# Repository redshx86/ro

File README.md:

The control box i made for my reverse osmosis filter. I doubt anyone needs this.

## Main display
Off -> Blank\
Idle -> filter total time, days\
Work -> filtering time, minutes\
Flush -> Spin\
No water -> "drY"\
Timeout -> "Err"\
Short press: Off->on, Flush/Nowater/Timeout->idle, Other->lamp on/off\
Long press: menu\

### Menu
OFF -> Turn off\
FLU -> Start manual flush\
C00 -> Filter total time, hrs/thousands\
C01 -> Filter work time, hrs/thousands\
C02 -> Total on time, hrs/thousands\
C03 -> Total run time, hrs/thousands\
C04 -> Total start count, pcs/thousands\
C05 -> Total flush count, pcs/thousands\
P00 -> Manual flushing time 0..60/1 min\
P01 -> Auto flushing time 0..900/10 sec\
P02 -> Work time flush threshold 0..990/10 min\
P03 -> Total time flush threshold 0..240/5 hr\
P04 -> Timeout 0..360/5 min\
P05 -> Nowater delay 0..60/1 sec\
P06 -> Extra work time after HP switch off 0..360/5 sec\
CLr -> Reset filter on time/work time (confirm yes/no)\
X.XX -> AIN_C voltage (ok=back)\
XX.X -> Input voltage (ok=back)\
Long press: edit parameter/ok\
Short press: next parameter\

### Parameter edit / confirm menu\
short press: increase value / toggle confirm\
long press: save\

### Parameter display\
short press: back to menu\
long press: back to main display\

## Board pinout
DIA -> low pressure switch\
DIB -> high pressure switch\
DQA -> pump + inlet valve\
DQB -> flush valve\
DQC -> lamp\

## ATmega328 fuses
int.RC 8MHz 0ms+6CK DIV8\
BOR@1.8V

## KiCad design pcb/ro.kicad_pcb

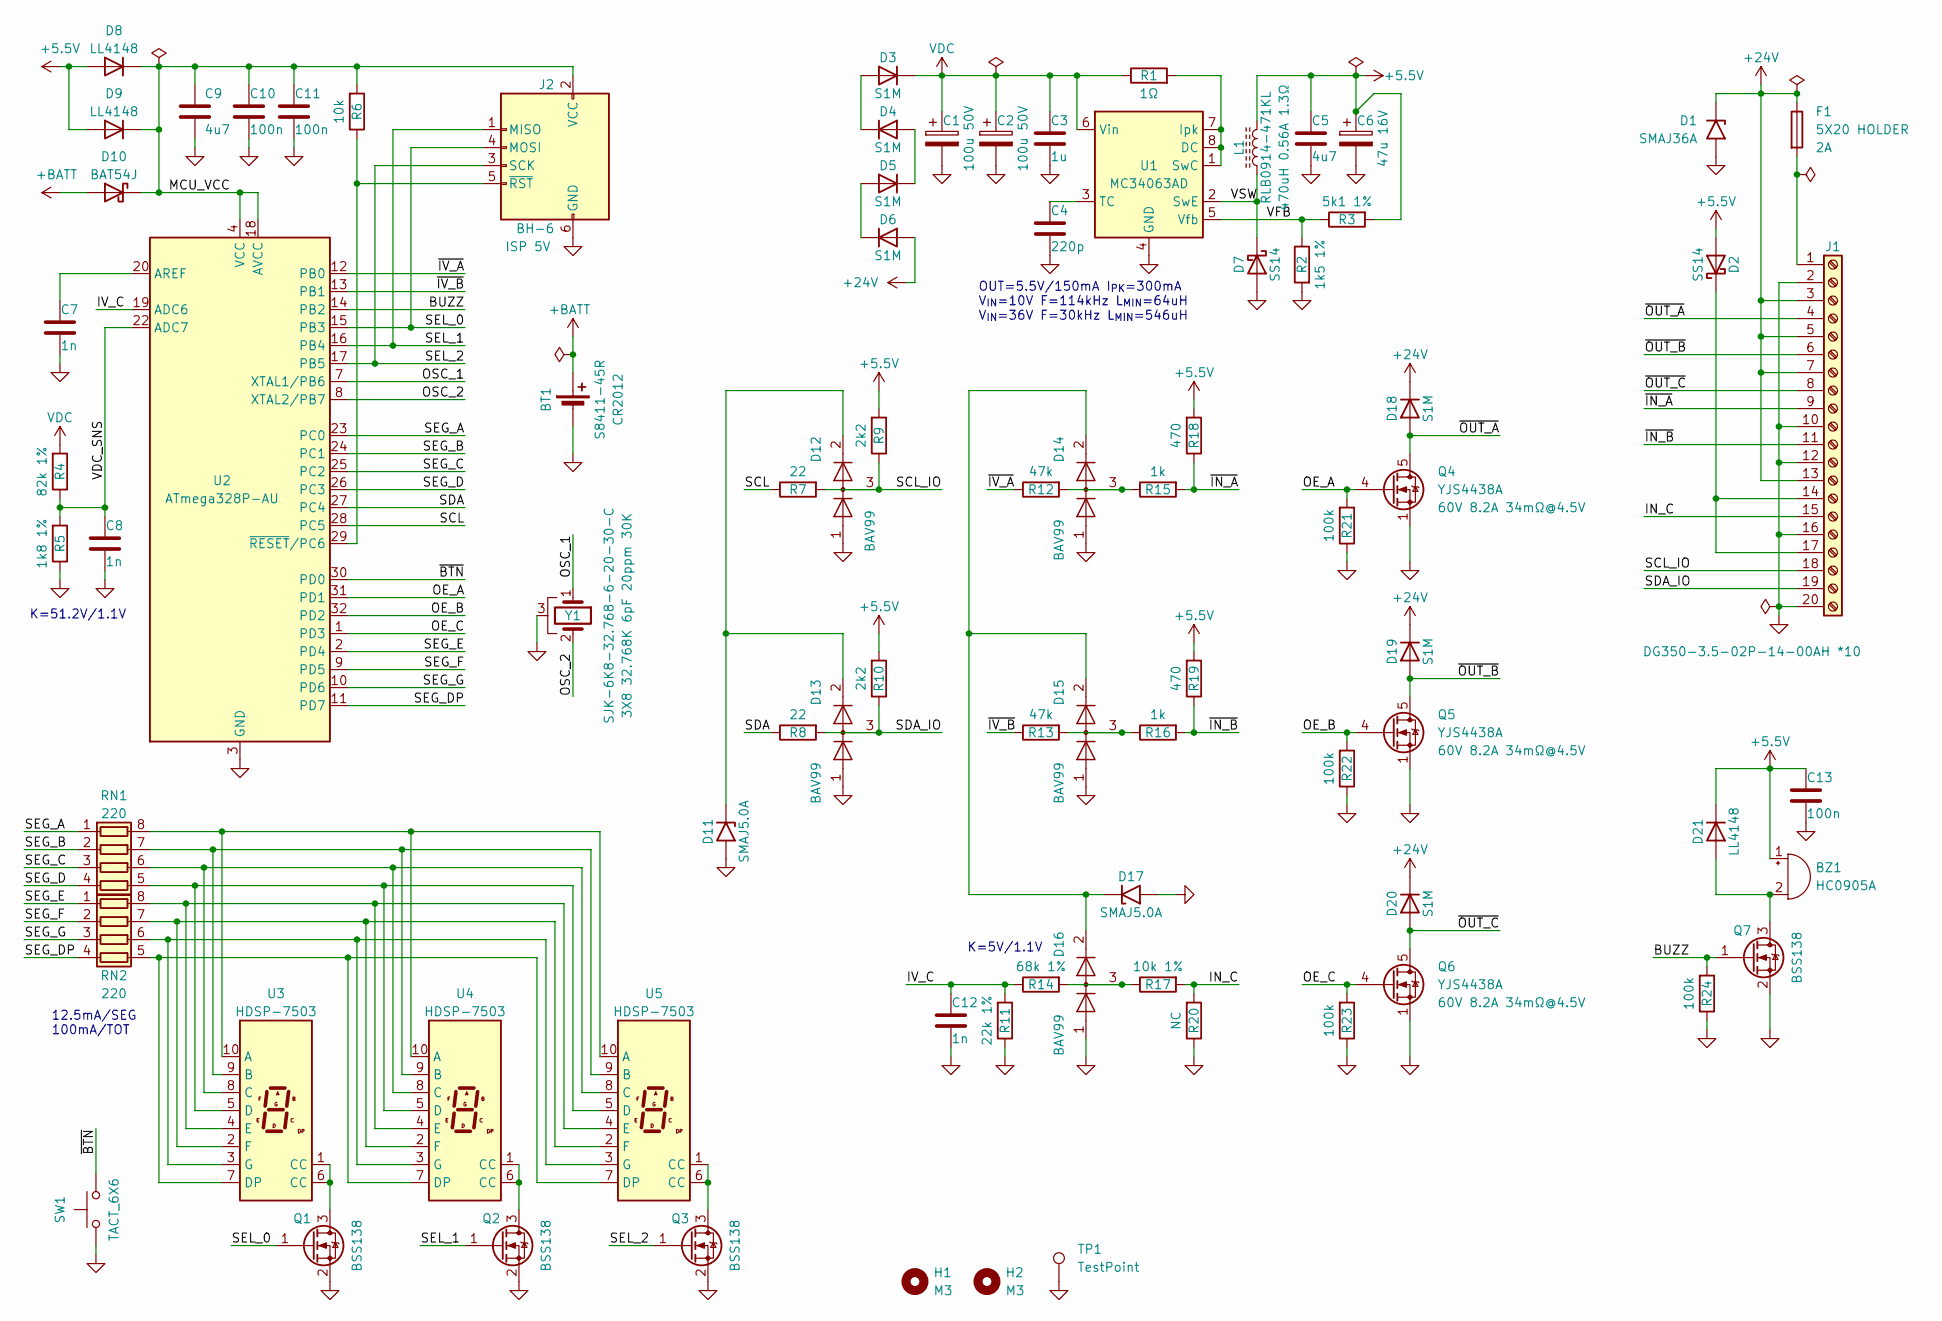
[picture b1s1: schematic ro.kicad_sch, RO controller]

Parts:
BT1: S8411-45R
BZ1: HC0905A; MagneticBuzzer_CUI_CST-931RP-A
C1, C2: 100u 50V; CP_Elec_8x10.5
C3: 1u; C_1206_3216Metric_Pad1.33x1.80mm_HandSolder
C4: 220p; C_0603_1608Metric_Pad1.08x0.95mm_HandSolder
C5, C9: 4u7; C_1206_3216Metric_Pad1.33x1.80mm_HandSolder
C6: 47u 16V; CP_EIA-7343-31_Kemet-D_Pad2.25x2.55mm_HandSolder
C7, C8, C12: 1n; C_0603_1608Metric_Pad1.08x0.95mm_HandSolder
C10, C11, C13: 100n; C_0603_1608Metric_Pad1.08x0.95mm_HandSolder
D1: SMAJ36A; D_SMA
D2, D7: SS14; D_SMA
D3, D4, D5, D6, D18, D19, D20: S1M; D_SMA
D8, D9, D21: LL4148; D_MiniMELF
D10: BAT54J; D_SOD-323_HandSoldering
D11, D17: SMAJ5.0A; D_SMA
D12, D13, D14, D15, D16: BAV99; SOT-23
F1: 5X20 HOLDER; Fuse_Clip_TE_520
H1, H2: M3; MountingHole_3.2mm_M3
J1: DG350-3.5-02P-14-00AH *10; TerminalBlock_4Ucon_1x20_P3.50mm_Horizontal
J2: BH-6; IDC-Header_2x03_P2.54mm_Vertical
L1: RLB0914-471KL; L_Radial_D8.7mm_P5.00mm_Fastron_07HCP
Q1, Q2, Q3, Q7: BSS138; SOT-23
Q4, Q5, Q6: YJS4438A; SOIC-8_3.9x4.9mm_P1.27mm
R1: 1Ω; R_1206_3216Metric_Pad1.30x1.75mm_HandSolder
R2: 1k5 1%; R_0603_1608Metric_Pad0.98x0.95mm_HandSolder
R3: 5k1 1%; R_0603_1608Metric_Pad0.98x0.95mm_HandSolder
R4: 82k 1%; R_0603_1608Metric_Pad0.98x0.95mm_HandSolder
R5: 1k8 1%; R_0603_1608Metric_Pad0.98x0.95mm_HandSolder
R6: 10k; R_0603_1608Metric_Pad0.98x0.95mm_HandSolder
R7, R8: 22; R_0603_1608Metric_Pad0.98x0.95mm_HandSolder
R9, R10: 2k2; R_0603_1608Metric_Pad0.98x0.95mm_HandSolder
R11: 22k 1%; R_0603_1608Metric_Pad0.98x0.95mm_HandSolder
R12, R13: 47k; R_0603_1608Metric_Pad0.98x0.95mm_HandSolder
R14: 68k 1%; R_0603_1608Metric_Pad0.98x0.95mm_HandSolder
R15, R16: 1k; R_0603_1608Metric_Pad0.98x0.95mm_HandSolder
R17: 10k 1%; R_0603_1608Metric_Pad0.98x0.95mm_HandSolder
R18, R19: 470; R_0603_1608Metric_Pad0.98x0.95mm_HandSolder
R20: NC; R_0603_1608Metric_Pad0.98x0.95mm_HandSolder
R21, R22, R23, R24: 100k; R_0603_1608Metric_Pad0.98x0.95mm_HandSolder
RN1, RN2: 220; R_Array_Convex_4x0603
SW1: TACT_6X6; SW_PUSH_6mm_H8mm
TP1: TestPoint; TestPoint_Bridge_Pitch2.54mm_Drill1.0mm
U1: MC34063AD; SOIC-8_3.9x4.9mm_P1.27mm
U2: ATmega328P-AU; TQFP-32_7x7mm_P0.8mm
U3, U4, U5: HDSP-7503; HDSP-A151
Y1: SJK-6K8-32.768-6-20-30-C; Crystal_C38-LF_D3.0mm_L8.0mm_Horizontal_1EP_style2

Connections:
+5.5V: BZ1.1 (+), C5.1, C6.1, C13.1, D2.2 (A), D8.2 (A), D9.2 (A), D21.1 (K), L1.1, R3.2, R9.2, R10.2, R18.2, R19.2
+24V: D1.1 (A1), D6.2 (A), D18.1 (K), D19.1 (K), D20.1 (K), F1.1, J1.3, J1.5, J1.7, J1.13
+BATT: BT1.1 (+), D10.2 (A)
/BUZZ: Q7.1 (G), R24.2, U2.14 (PB2)
/IN_C: J1.15, R17.2, R20.2
/IV_C: C12.1, R11.2, R14.1, U2.19 (ADC6)
/MCU_VCC: C9.1, C10.1, C11.1, D8.1 (K), D9.1 (K), D10.1 (K), J2.2 (VCC), R6.2, U2.4 (VCC), U2.6 (VCC), U2.18 (AVCC)
/OE_A: Q4.4 (G), R21.2, U2.31 (PD1)
/OE_B: Q5.4 (G), R22.2, U2.32 (PD2)
/OE_C: Q6.4 (G), R23.2, U2.1 (PD3)
/OSC_1: U2.7 (XTAL1/PB6), Y1.1
/OSC_2: U2.8 (XTAL2/PB7), Y1.2
/SCL: R7.1, U2.28 (PC5)
/SCL_IO: D12.3 (K), J1.18, R7.2, R9.1
/SDA: R8.1, U2.27 (PC4)
/SDA_IO: D13.3 (K), J1.19, R8.2, R10.1
/SEG_A: RN1.1 (R1.1), U2.23 (PC0)
/SEG_B: RN1.2 (R2.1), U2.24 (PC1)
/SEG_C: RN1.3 (R3.1), U2.25 (PC2)
/SEG_D: RN1.4 (R4.1), U2.26 (PC3)
/SEG_DP: RN2.4 (R4.1), U2.11 (PD7)
/SEG_E: RN2.1 (R1.1), U2.2 (PD4)
/SEG_F: RN2.2 (R2.1), U2.9 (PD5)
/SEG_G: RN2.3 (R3.1), U2.10 (PD6)
/SEL_0: J2.4 (MOSI), Q1.1 (G), U2.15 (PB3)
/SEL_1: J2.1 (MISO), Q2.1 (G), U2.16 (PB4)
/SEL_2: J2.3 (SCK), Q3.1 (G), U2.17 (PB5)
/VDC_SNS: C8.1, R4.1, R5.2, U2.22 (ADC7)
/VFB: R2.1, R3.1, U1.5 (Vfb)
/VSW: D7.1 (K), L1.2, U1.2 (SwE)
/~BTN: SW1.2, U2.30 (PD0)
/~IN_A: J1.9, R15.2, R18.1
/~IN_B: J1.11, R16.2, R19.1
/~IV_A: R12.1, U2.12 (PB0)
/~IV_B: R13.1, U2.13 (PB1)
/~OUT_A: D18.2 (A), J1.4, Q4.5 (D), Q4.6 (D), Q4.7 (D), Q4.8 (D)
/~OUT_B: D19.2 (A), J1.6, Q5.5 (D), Q5.6 (D), Q5.7 (D), Q5.8 (D)
/~OUT_C: D20.2 (A), J1.8, Q6.5 (D), Q6.6 (D), Q6.7 (D), Q6.8 (D)
GND: BT1.2 (-), C1.2, C2.2, C3.2, C4.2, C5.2, C6.2, C7.2, C8.2, C9.2, C10.2, C11.2, C12.2, C13.2, D1.2 (A2), D7.2 (A), D11.2 (A2), D12.1 (K), D13.1 (K), D14.1 (K), D15.1 (K), D16.1 (K), D17.2 (A2), J1.2, J1.10, J1.12, J1.16, J1.20, J2.6 (GND), Q1.2 (S), Q2.2 (S), Q3.2 (S), Q4.1 (S), Q4.2 (S), Q4.3 (S), Q5.1 (S), Q5.2 (S), Q5.3 (S), Q6.1 (S), Q6.2 (S), Q6.3 (S), Q7.2 (S), R2.2, R5.1, R11.1, R20.1, R21.1, R22.1, R23.1, R24.1, SW1.1, TP1.1, U1.4 (GND), U2.3 (GND), U2.5 (GND), U2.21 (GND), Y1.3
unnamed: BZ1.2 (-), D21.2 (A), Q7.3 (D)
unnamed: D2.1 (K), J1.14, J1.17
unnamed: D3.2 (A), D4.1 (K)
unnamed: D4.2 (A), D5.1 (K)
unnamed: D5.2 (A), D6.1 (K)
unnamed: D11.1 (A1), D12.2 (A), D13.2 (A)
unnamed: D14.2 (A), D15.2 (A), D16.2 (A), D17.1 (A1)
unnamed: D14.3 (K), R12.2, R15.1
unnamed: D15.3 (K), R13.2, R16.1
unnamed: D16.3 (K), R14.2, R17.1
unnamed: F1.2, J1.1
unnamed: J2.5 (~RST), R6.1, U2.29 (~RESET/PC6)
unnamed: Q1.3 (D), U3.1 (CC), U3.6 (CC)
unnamed: Q2.3 (D), U4.1 (CC), U4.6 (CC)
unnamed: Q3.3 (D), U5.1 (CC), U5.6 (CC)
unnamed: RN1.8 (R1.2), U3.10 (A), U4.10 (A), U5.10 (A)
unnamed: RN1.7 (R2.2), U3.9 (B), U4.9 (B), U5.9 (B)
unnamed: RN1.6 (R3.2), U3.8 (C), U4.8 (C), U5.8 (C)
unnamed: RN1.5 (R4.2), U3.5 (D), U4.5 (D), U5.5 (D)
unnamed: RN2.8 (R1.2), U3.4 (E), U4.4 (E), U5.4 (E)
unnamed: RN2.7 (R2.2), U3.2 (F), U4.2 (F), U5.2 (F)
unnamed: RN2.6 (R3.2), U3.3 (G), U4.3 (G), U5.3 (G)
unnamed: RN2.5 (R4.2), U3.7 (DP), U4.7 (DP), U5.7 (DP)
unnamed: R1.2, U1.1 (SwC), U1.7 (Ipk), U1.8 (DC)
unnamed: C4.1, U1.3 (TC)
unnamed: C7.1, U2.20 (AREF)
VDC: C1.1, C2.1, C3.1, D3.1 (K), R1.1, R4.2, U1.6 (Vin)

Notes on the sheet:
K=5V/1.1V
OUT=5.5V/150mA I_{PK}=300mA V_{IN}=10V F=114kHz L_{MIN}=64uH V_{IN}=36V F=30kHz L_{MIN}=546uH
12.5mA/SEG 100mA/TOT
K=51.2V/1.1V

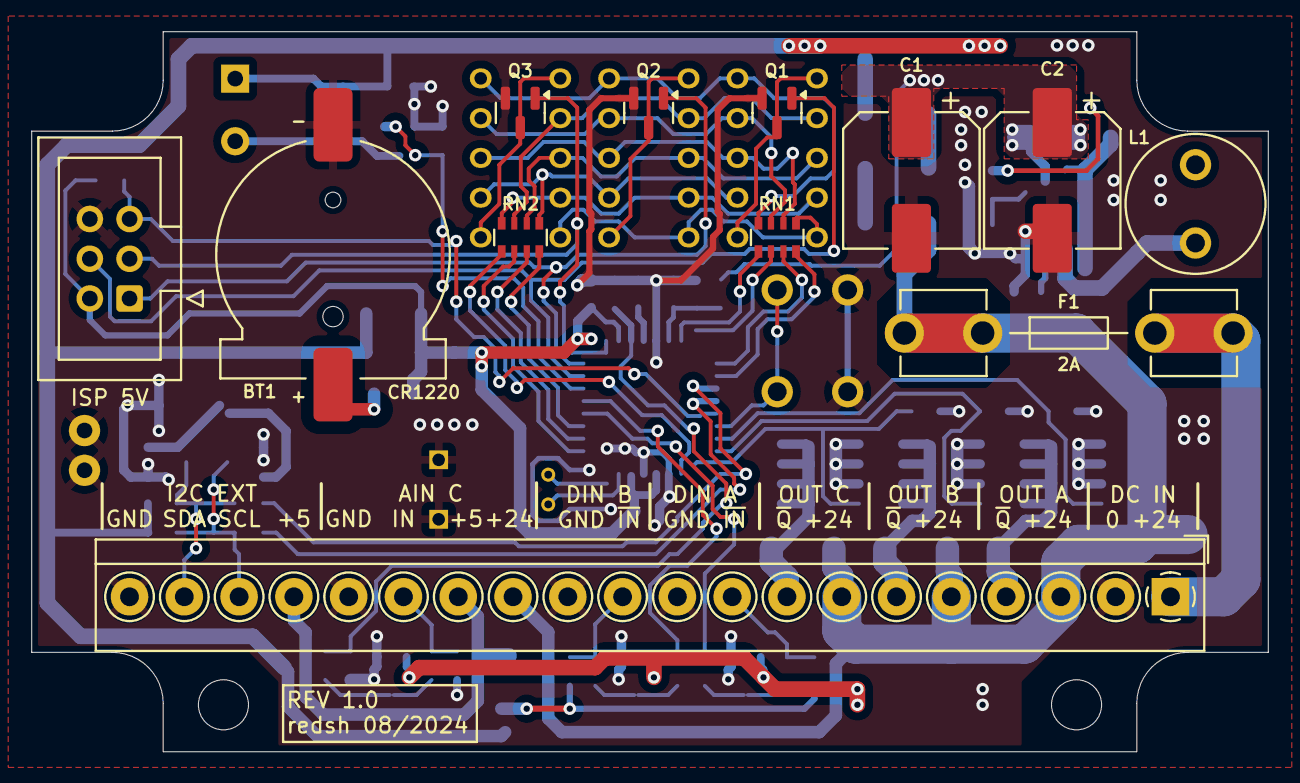
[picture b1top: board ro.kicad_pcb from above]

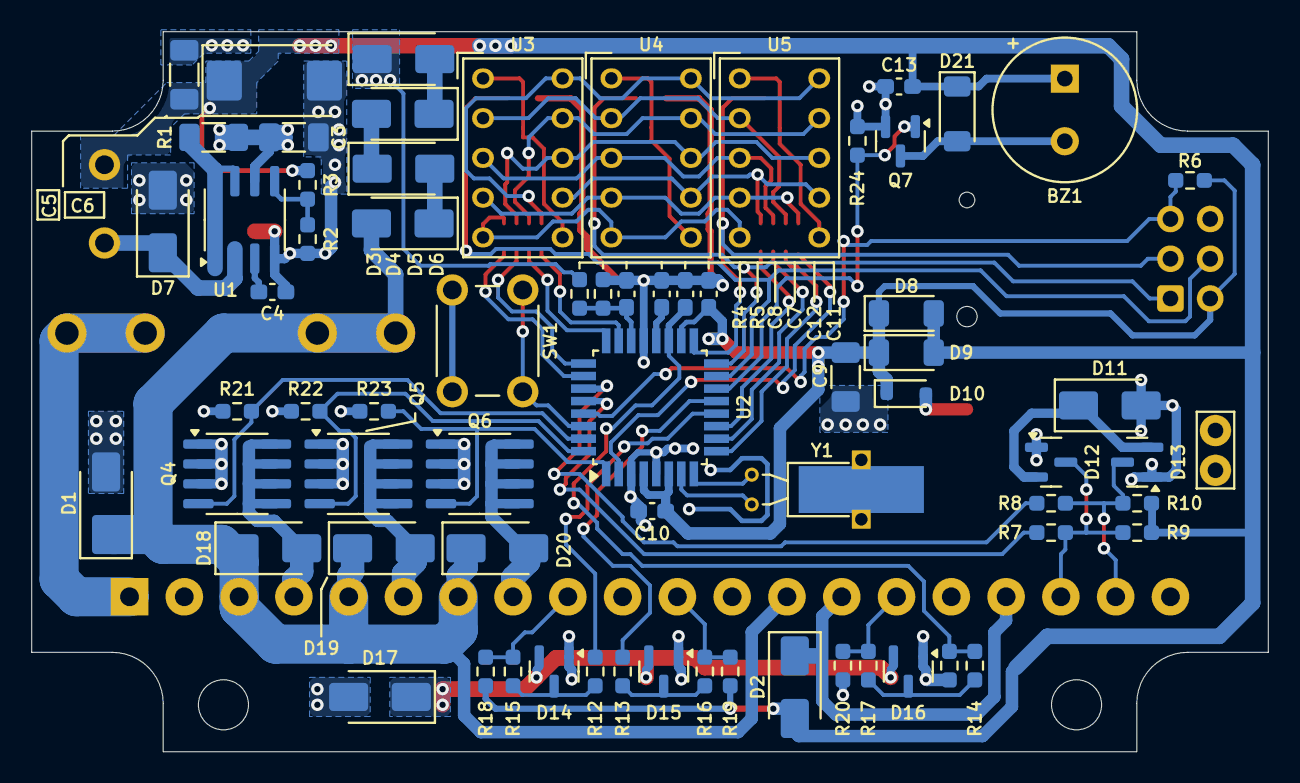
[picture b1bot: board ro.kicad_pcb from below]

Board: 2 copper layers, 79.0 x 46.0 mm, 83 parts (71 on the bottom side), 66 nets.

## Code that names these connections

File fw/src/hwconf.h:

// -------------------------------------------------------------------------------------------------
// RO controller MCU pinout

#pragma once

// -------------------------------------------------------------------------------------------------
// Discrete input

#define DI_PIN				PINB
#define DI_A_N				(1<<PB0)
#define DI_B_N				(1<<PB1)

#define DI_A_IS_ON()		!(DI_PIN & DI_A_N)
#define DI_B_IS_ON()		!(DI_PIN & DI_B_N)

// -------------------------------------------------------------------------------------------------
// Discrete output

#define DQ_PORT				PORTD
#define DQ_PIN				PIND
#define DQ_A_P				(1<<PD1)
#define DQ_B_P				(1<<PD2)
#define DQ_C_P				(1<<PD3)

#define DQ_A_ON()			DQ_PORT |= DQ_A_P
#define DQ_A_OFF()			DQ_PORT &= ~DQ_A_P
#define DQ_A_TGL()			DQ_PIN = DQ_A_P
#define DQ_A_IS_ON()		(DQ_PORT & DQ_A_P)

#define DQ_B_ON()			DQ_PORT |= DQ_B_P
#define DQ_B_OFF()			DQ_PORT &= ~DQ_B_P
#define DQ_B_TGL()			DQ_PIN = DQ_B_P
#define DQ_B_IS_ON()		(DQ_PORT & DQ_B_P)

#define DQ_C_ON()			DQ_PORT |= DQ_C_P
#define DQ_C_OFF()			DQ_PORT &= ~DQ_C_P
#define DQ_C_TGL()			DQ_PIN = DQ_C_P
#define DQ_C_IS_ON()		(DQ_PORT & DQ_C_P)

// -------------------------------------------------------------------------------------------------
// 7-segment display

#define SEG_3_0_PORT		PORTC	// PORTC[3:0]=SEG[3:0]
#define SEG_7_4_PORT		PORTD	// PORTD[7:4]=SEG[7:4]
#define SEG_3_0_P			0x0F
#define SEG_7_4_P			0xF0

#define SEL_PORT			PORTB
#define SEL_0_BIT			PB3
#define SEL_1_BIT			PB4
#define SEL_2_BIT			PB5
#define SEL_0_P				(1<<SEL_0_BIT)
#define SEL_1_P				(1<<SEL_1_BIT)
#define SEL_2_P				(1<<SEL_2_BIT)
#define SEL_ALL				(SEL_0_P|SEL_1_P|SEL_2_P)

#define SEG_WRITE(data) do {												\
		SEG_3_0_PORT = (SEG_3_0_PORT & ~SEG_3_0_P) | ((data) & SEG_3_0_P);	\
		SEG_7_4_PORT = (SEG_7_4_PORT & ~SEG_7_4_P) | ((data) & SEG_7_4_P);	\
	} while(0)

#define SEL_OFF()			SEL_PORT &= ~(SEL_0_P|SEL_1_P|SEL_2_P)
#define SEL_0_ON()			SEL_PORT |= SEL_0_P
#define SEL_1_ON()			SEL_PORT |= SEL_1_P
#define SEL_2_ON()			SEL_PORT |= SEL_2_P

// -------------------------------------------------------------------------------------------------
// Push button

#define BTN_PIN				PIND
#define BTN_PORT			PORTD
#define BTN_DDR				DDRD
#define BTN_N				(1<<PD0)

#define BTN_ENABLE() do {		\
		BTN_DDR &= ~BTN_N;		\
		BTN_PORT |= BTN_N;		\
	} while(0)
#define BTN_DISABLE() do {		\
		BTN_PORT &= ~BTN_N;		\
		BTN_DDR |= BTN_N;		\
	} while(0)
#define BTN_IS_PSH()		!(BTN_PIN & BTN_N)

// -------------------------------------------------------------------------------------------------
// Buzzer (3.2kHz)

#define BUZZ_FREQ			3200
#define BUZZ_P				(1<<PB2)	// OC1B

#define BUZZ_ON()			TCCR1A |= 1<<COM1B1
#define BUZZ_OFF()			TCCR1A &= ~(1<<COM1B1)
#define BUZZ_IS_ON()		(TCCR1A & (1<<COM1B1))

// Timer1:FastPWM(TOP=OCR1A) @ F_CPU
// OC1B -> Buzzer
#define BUZZ_ENABLE() do {							\
		PRR &= ~(1<<PRTIM1);						\
		OCR1A = F_CPU/BUZZ_FREQ-1;					\
		OCR1B = F_CPU/BUZZ_FREQ/2;					\
		TCCR1A = (1<<WGM11)|(1<<WGM10);				\
		TCCR1B = (1<<WGM13)|(1<<WGM12)|(1<<CS10);	\
	} while(0)
#define BUZZ_DISABLE() do {							\
		BUZZ_OFF();									\
		TCCR1B &= ~(1<<CS10);						\
		PRR |= 1<<PRTIM1;							\
	} while(0)

// -------------------------------------------------------------------------------------------------

// Timer0:Normal @ F_CPU/64
// OC0A -> Sys tick and Display
#define TICK_DISP_ENABLE() do {						\
		PRR &= ~(1<<PRTIM0);						\
		TCCR0B = (1<<CS01)|(1<<CS00);				\
		TIMSK0 = 1<<OCIE0A;							\
	} while(0)
#define TICK_DISP_DISABLE() do {					\
		TCCR0B = 0;									\
		PRR |= 1<<PRTIM0;							\
		SEG_WRITE(0);								\
		SEL_OFF();									\
	} while(0)

// -------------------------------------------------------------------------------------------------

// Timer2:Async @ F_32K/256
// OVF -> RTC tick
#define RTC_TICK_INIT() do {						\
		ASSR = 1<<AS2;								\
		TCNT2 = 0;									\
		OCR2A = 0;									\
		OCR2B = 0;									\
		TCCR2A = 0;									\
		TCCR2B = (1<<CS22)|(1<<CS21);				\
		while(ASSR & 0x1f)							\
			;										\
		TIMSK2 = 1<<TOIE2;							\
	} while(0)

// -------------------------------------------------------------------------------------------------
// ADC

#define ADMUX_AIN_C			((1<<REFS1)|(1<<REFS0)|6)	// 5.00V FS
#define ADMUX_VDC			((1<<REFS1)|(1<<REFS0)|7)	// 51.2V FS

// -------------------------------------------------------------------------------------------------

//#define PORTB_INIT		(0)
#define DDRB_INIT			(BUZZ_P|SEL_0_P|SEL_1_P|SEL_2_P)
//#define PORTC_INIT		(0)
#define DDRC_INIT			(SEG_3_0_P)
//#define PORTD_INIT		(0)
#define DDRD_INIT			(BTN_N|DQ_A_P|DQ_B_P|DQ_C_P|SEG_7_4_P)

// -------------------------------------------------------------------------------------------------

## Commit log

2024-09-13 upload
